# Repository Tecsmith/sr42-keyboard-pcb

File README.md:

# SR42 Keyboard

<p align="center">
Please refer to the <a href="https://github.com/Tecsmith/sr42-keyboard">project home</a> page for README and documentation.
</p>

---

<p align="center">
  <br>
  <b>Please Note:</b> This project is design complete, but has not been prototyped to validate. Build at your own risk.
</p>

---

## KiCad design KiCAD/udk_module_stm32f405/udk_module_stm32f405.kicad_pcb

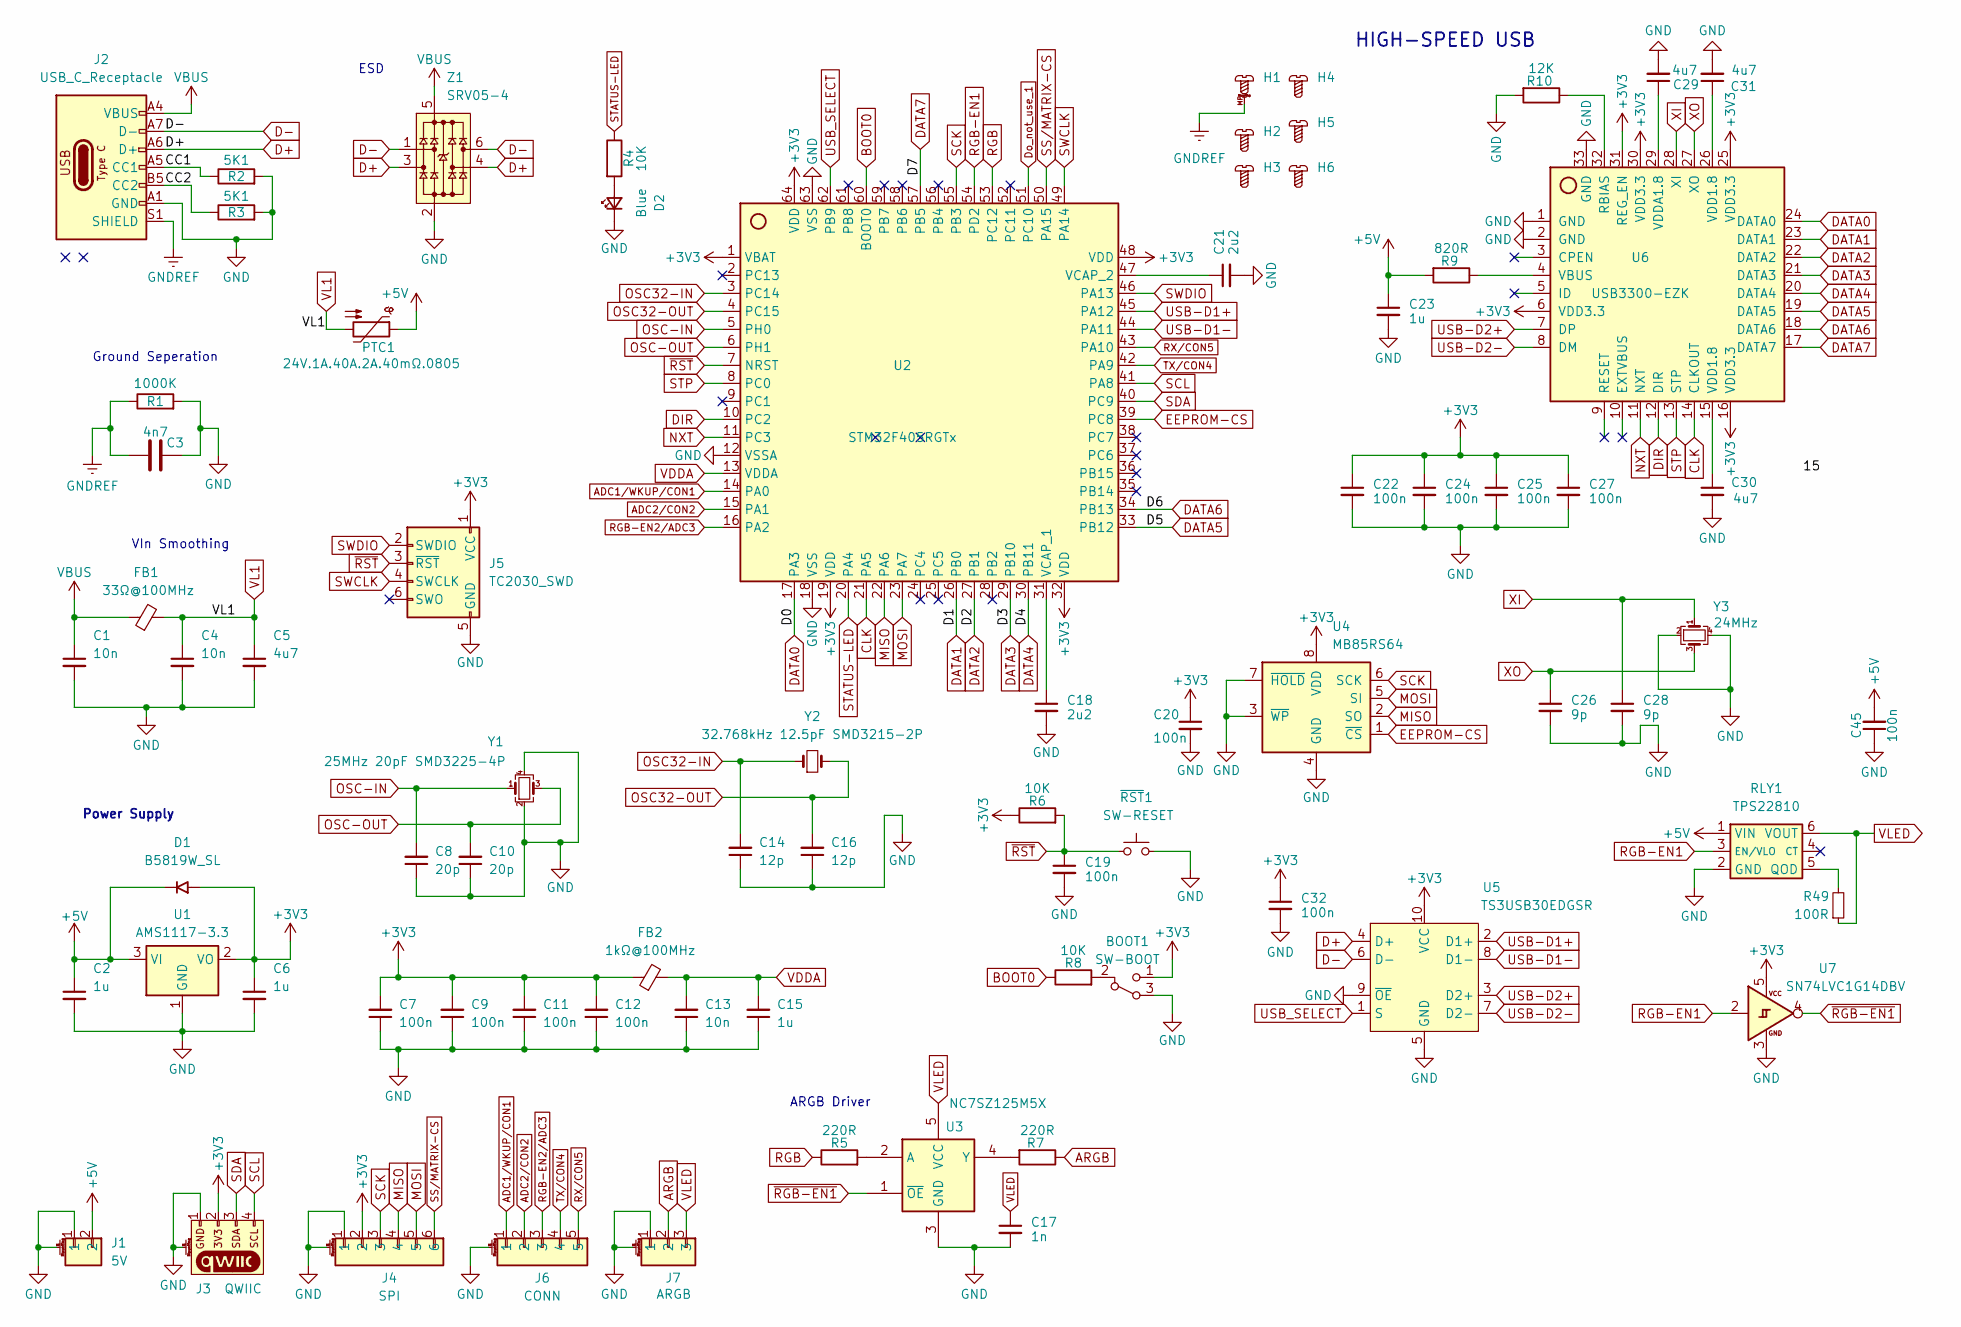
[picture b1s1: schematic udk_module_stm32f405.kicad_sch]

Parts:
BOOT1: SW-BOOT; SW_SPDT_Shouhan_MSK12C02; LCSC C431540
C1, C4, C13: 10n; C_0603_1608Metric
C2, C6, C15, C23: 1u; C_0603_1608Metric
C3: 4n7; C_0805_2012Metric_Pad1.18x1.45mm_HandSolder
C5, C29, C30, C31: 4u7; C_0603_1608Metric
C7, C9, C11, C12, C19, C20, C24, C25, C27, C32, C45: 100n; C_0603_1608Metric
C8, C10: 20p; C_0603_1608Metric
C14, C16: 12p; C_0603_1608Metric
C17: 1n; C_0603_1608Metric
C18, C21: 2u2; C_0603_1608Metric
C22: 100n; C_0603_1608Metric; Tolerance 100%
C26, C28: 9p; C_0603_1608Metric
D1: B5819W_SL; D_SOD-123
D2: Blue; LED_0603_1608Metric_Blue
FB1: 33Ω@100MHz; L_0603_1608Metric; LCSC C88984
FB2: 1kΩ@100MHz; L_0603_1608Metric
H1: Mount_M2_Rel
H2, H3, H4, H5, H6: Hole_M2
J1: 5V; JST_SH_SM02B-SRSS-TB_1x02-1MP_P1.00mm_Horizontal
J2: USB_C_Receptacle; USB_C_Receptacle_HRO_TYPE-C-31-M-12
J3: QWIIC; JST_SH_SM04B-SRSS-TB_1x04-1MP_P1.00mm_Horizontal
J4: SPI; JST_SH_SM06B-SRSS-TB_1x06-1MP_P1.00mm_Horizontal
J5: TC2030_SWD; CON_TC2030_outlined
J6: CONN; JST_SH_SM05B-SRSS-TB_1x05-1MP_P1.00mm_Horizontal
J7: ARGB; JST_SH_SM03B-SRSS-TB_1x03-1MP_P1.00mm_Horizontal
PTC1: 24V.1A.40A.2A.40mΩ.0805; L_Coilcraft_0805HQ_2012Metric; LCSC C42369218
R1: 1000K; R_0805_2012Metric_Pad1.20x1.40mm_HandSolder
R2, R3: 5K1; R_0603_1608Metric
R4, R6, R8: 10K; R_0603_1608Metric
R5, R7: 220R; R_0603_1608Metric
R9: 820R; R_0603_1608Metric
R10: 12K; R_0603_1608Metric
R49: 100R; R_0603_1608Metric
RLY1: TPS22810; SOT-23-6; LCSC C205990
U1: AMS1117-3.3; SOT-223-3_TabPin2
U2: STM32F405RGTx; LQFP-64_10x10mm_P0.5mm
U3: NC7SZ125M5X; SOT-23-5
U4: MB85RS64; SOIC-8_5.3x5.3mm_P1.27mm
U5: TS3USB30EDGSR; VSSOP-10_3x3mm_P0.5mm
U6: USB3300-EZK; QFN-32-1EP_5x5mm_P0.5mm_EP3.45x3.45mm
U7: SN74LVC1G14DBV; SOT-23-5
Y1: 25MHz 20pF SMD3225-4P; Crystal_SMD_3225-4Pin_3.2x2.5mm; LCSC C91738
Y2: 32.768kHz 12.5pF SMD3215-2P; Crystal_SMD_3215-2Pin_3.2x1.5mm; LCSC C156245
Y3: 24MHz; Crystal_SMD_3225-4Pin_3.2x2.5mm
Z1: SRV05-4; TSOP-6_1.65x3.05mm_P0.95mm
~{RST}1: SW-RESET; SW_SPST_CK_KMS2xxGP

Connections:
+3V3: BOOT1.1 (A), C6.1, C7.2, C9.2, C11.2, C12.2, C20.1, C22.1, C24.1, C25.1, C27.1, C32.1, D1.2 (A), FB2.1, J3.2, J4.2, J5.1 (VCC), R6.1, U1.2 (VO), U2.1 (VBAT), U2.19 (VDD), U2.32 (VDD), U2.48 (VDD), U2.64 (VDD), U4.8 (VDD), U5.10 (VCC), U6.6 (VDD3.3), U6.16 (VDD3.3), U6.25 (VDD3.3), U6.30 (VDD3.3), U6.31 (REG_EN), U7.5
+5V: C2.1, C23.1, C45.2, D1.1 (K), J1.2, PTC1.1, R9.2, RLY1.1 (VIN), U1.3 (VI)
/CC1: J2.A5 (CC1), R2.1
/CC2: J2.B5 (CC2), R3.1
ADC1/WKUP/CON1: J6.1, U2.14 (PA0)
ADC2/CON2: J6.2, U2.15 (PA1)
ARGB: J7.2, R7.1
BOOT0: R8.1, U2.60 (BOOT0)
CLK: U2.21 (PA5), U6.14 (CLKOUT)
D+: J2.A6 (D+), J2.B6 (D+), U5.4 (D+), Z1.3, Z1.4
D-: J2.A7 (D-), J2.B7 (D-), U5.6 (D-), Z1.1, Z1.6
DATA0: U2.17 (PA3), U6.24 (DATA0)
DATA1: U2.26 (PB0), U6.23 (DATA1)
DATA2: U2.27 (PB1), U6.22 (DATA2)
DATA3: U2.29 (PB10), U6.21 (DATA3)
DATA4: U2.30 (PB11), U6.20 (DATA4)
DATA5: U2.33 (PB12), U6.19 (DATA5)
DATA6: U2.34 (PB13), U6.18 (DATA6)
DATA7: U2.57 (PB5), U6.17 (DATA7)
DIR: U2.10 (PC2), U6.12 (DIR)
Do_not_use_1: U2.51 (PC10)
EEPROM-CS: U2.39 (PC8), U4.1 (~CS)
GND: BOOT1.3 (C), C1.2, C2.2, C3.2, C4.2, C5.2, C6.2, C7.1, C8.1, C9.1, C10.1, C11.1, C12.1, C13.1, C14.1, C15.1, C16.1, C17.2, C18.2, C19.2, C20.2, C21.2, C22.2, C23.2, C24.2, C25.2, C26.2, C27.2, C28.2, C29.2, C30.2, C31.2, C32.2, C45.1, D2.1 (K), J1.1, J1.MP, J2.A1 (GND), J2.A12 (GND), J2.B1 (GND), J2.B12 (GND), J3.1, J3.MP, J4.1, J4.MP, J5.5 (GND), J6.MP, J7.1, J7.MP, R1.2, R2.2, R3.2, R10.2, RLY1.2 (GND), U1.1 (GND), U2.12 (VSSA), U2.18 (VSS), U2.63 (VSS), U3.3 (GND), U4.3 (~WP), U4.4 (GND), U4.7 (~HOLD), U5.5 (GND), U5.9 (~OE), U6.1 (GND), U6.2 (GND), U6.33 (GND), U7.3, Y1.2, Y1.4, Y3.2, Y3.4, Z1.2, ~{RST}1.2
GNDREF: C3.1, H1.MP, J2.S1 (SHIELD), R1.1
MISO: J4.4, U2.22 (PA6), U4.2 (SO)
MOSI: J4.5, U2.23 (PA7), U4.5 (SI)
NXT: U2.11 (PC3), U6.11 (NXT)
unnamed: BOOT1.2 (B), R8.2
unnamed: C30.1, U6.15 (VDD1.8)
unnamed: C31.1, U6.26 (VDD1.8)
unnamed: D2.2 (A), R4.2
unnamed: R49.2, RLY1.5 (QOD)
unnamed: C18.1, U2.31 (VCAP_1)
unnamed: C21.1, U2.47 (VCAP_2)
unnamed: R5.2, U3.2 (A)
unnamed: R7.2, U3.4 (Y)
unnamed: R10.1, U6.32 (RBIAS)
unnamed: R9.1, U6.4 (VBUS)
unnamed: C29.1, U6.29 (VDDA1.8)
OSC32-IN: C14.2, U2.3 (PC14), Y2.1
OSC32-OUT: C16.2, U2.4 (PC15), Y2.2
OSC-IN: C8.2, U2.5 (PH0), Y1.1
OSC-OUT: C10.2, U2.6 (PH1), Y1.3
RGB: R5.1, U2.53 (PC12)
RGB-EN1: RLY1.3 (EN/VLO), U2.54 (PD2), U7.2
RGB-EN2/ADC3: J6.3, U2.16 (PA2)
RX/CON5: J6.5, U2.43 (PA10)
SCK: J4.3, U2.55 (PB3), U4.6 (SCK)
SCL: J3.4, U2.41 (PA8)
SDA: J3.3, U2.40 (PC9)
SS/MATRIX-CS: J4.6, U2.50 (PA15)
STATUS-LED: R4.1, U2.20 (PA4)
STP: U2.8 (PC0), U6.13 (STP)
SWCLK: J5.4 (SWCLK), U2.49 (PA14)
SWDIO: J5.2 (SWDIO), U2.46 (PA13)
TX/CON4: J6.4, U2.42 (PA9)
USB-D1+: U2.45 (PA12), U5.2 (D1+)
USB-D1-: U2.44 (PA11), U5.8 (D1-)
USB-D2+: U5.3 (D2+), U6.7 (DP)
USB-D2-: U5.7 (D2-), U6.8 (DM)
USB_SELECT: U2.62 (PB9), U5.1 (S)
VBUS: C1.1, FB1.1, J2.A4 (VBUS), J2.A9 (VBUS), J2.B4 (VBUS), J2.B9 (VBUS), Z1.5
VDDA: C13.2, C15.2, FB2.2, U2.13 (VDDA)
VL1: C4.1, C5.1, FB1.2, PTC1.2
VLED: C17.1, J7.3, R49.1, RLY1.6 (VOUT), U3.5 (VCC)
XI: C28.1, U6.28 (XI), Y3.1
XO: C26.1, U6.27 (XO), Y3.3
~RGB-EN1: U3.1 (~OE), U7.4
~RST: C19.1, J5.3 (~RST), R6.2, U2.7 (NRST), ~{RST}1.1

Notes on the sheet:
ESD
Ground Seperation
VIn Smoothing
Power Supply
ARGB Driver
HIGH-SPEED USB

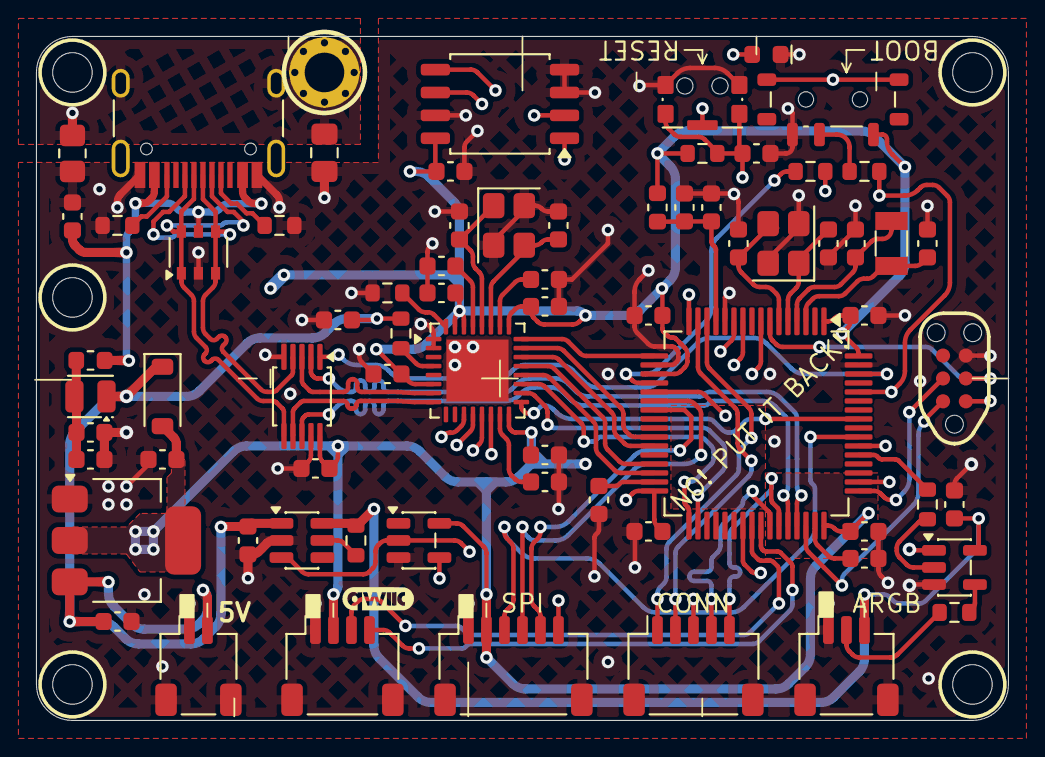
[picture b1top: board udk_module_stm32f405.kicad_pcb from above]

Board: 4 copper layers, 54.0 x 38.0 mm, 75 parts (0 on the bottom side), 68 nets.

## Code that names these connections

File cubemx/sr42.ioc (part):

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Mcu.Name=STM32F405RGTx
Mcu.Package=LQFP64
Mcu.UserName=STM32F405RGTx
PA0-WKUP.GPIOParameters=GPIO_Label
PA0-WKUP.GPIO_Label=ADC1/WKUP
PA0-WKUP.Signal=ADCx_IN0
PA1.GPIOParameters=GPIO_Label
PA1.GPIO_Label=ADC2
PA1.Signal=ADCx_IN1
PA10.GPIOParameters=GPIO_Label
PA10.GPIO_Label=RX/CON5
PA10.Mode=Asynchronous
PA10.Signal=USART1_RX
PA11.GPIOParameters=GPIO_Label
PA11.GPIO_Label=USB-D1-
PA11.Mode=Device_Only
PA11.Signal=USB_OTG_FS_DM
PA12.GPIOParameters=GPIO_Label
PA12.GPIO_Label=USB-D1+
PA12.Mode=Device_Only
PA12.Signal=USB_OTG_FS_DP
PA13.GPIOParameters=GPIO_Label
PA13.GPIO_Label=SWDIO
PA13.Mode=Serial_Wire
PA13.Signal=SYS_JTMS-SWDIO
PA14.GPIOParameters=GPIO_Label
PA14.GPIO_Label=SWCLK
PA14.Mode=Serial_Wire
PA14.Signal=SYS_JTCK-SWCLK
PA15.GPIOParameters=GPIO_Label
PA15.GPIO_Label=SS/MATRIX-CS
PA15.Mode=NSS_Signal_Hard_Output
PA15.Signal=SPI1_NSS
PA2.GPIOParameters=GPIO_Label
PA2.GPIO_Label=RGB-EN2/ADC3
PA2.Signal=ADCx_IN2
PA3.GPIOParameters=GPIO_Label
PA3.GPIO_Label=DATA0
PA3.Mode=Device_HS
PA3.Signal=USB_OTG_HS_ULPI_D0
PA4.GPIOParameters=GPIO_Label
PA4.GPIO_Label=STATUS-LED
PA4.Signal=GPIO_Output
PA5.GPIOParameters=GPIO_Label
PA5.GPIO_Label=CLK
PA5.Mode=Device_HS
PA5.Signal=USB_OTG_HS_ULPI_CK
PA6.GPIOParameters=GPIO_Label
PA6.GPIO_Label=MISO
PA6.Mode=Full_Duplex_Master
PA6.Signal=SPI1_MISO
PA7.GPIOParameters=GPIO_Label
PA7.GPIO_Label=MOSI
PA7.Mode=Full_Duplex_Master
PA7.Signal=SPI1_MOSI
PA8.GPIOParameters=GPIO_Label
PA8.GPIO_Label=SCL
PA8.Mode=I2C
PA8.Signal=I2C3_SCL
PA9.GPIOParameters=GPIO_Label
PA9.GPIO_Label=TX/CON4
PA9.Mode=Asynchronous
PA9.Signal=USART1_TX
PB0.GPIOParameters=GPIO_Label
PB0.GPIO_Label=DATA1
PB0.Mode=Device_HS
PB0.Signal=USB_OTG_HS_ULPI_D1
PB1.GPIOParameters=GPIO_Label
PB1.GPIO_Label=DATA2
PB1.Mode=Device_HS
PB1.Signal=USB_OTG_HS_ULPI_D2
PB10.GPIOParameters=GPIO_Label
PB10.GPIO_Label=DATA3
PB10.Mode=Device_HS
PB10.Signal=USB_OTG_HS_ULPI_D3
PB11.GPIOParameters=GPIO_Label
PB11.GPIO_Label=DATA4
PB11.Mode=Device_HS
PB11.Signal=USB_OTG_HS_ULPI_D4
PB12.GPIOParameters=GPIO_Label
PB12.GPIO_Label=DATA5
PB12.Mode=Device_HS
PB12.Signal=USB_OTG_HS_ULPI_D5
PB13.GPIOParameters=GPIO_Label
PB13.GPIO_Label=DATA6
PB13.Mode=Device_HS
PB13.Signal=USB_OTG_HS_ULPI_D6
PB3.GPIOParameters=GPIO_Label
PB3.GPIO_Label=SCK
PB3.Mode=Full_Duplex_Master
PB3.Signal=SPI1_SCK
PB5.GPIOParameters=GPIO_Label
PB5.GPIO_Label=DATA7
PB5.Mode=Device_HS
PB5.Signal=USB_OTG_HS_ULPI_D7
PB9.GPIOParameters=GPIO_Label
PB9.GPIO_Label=USB-SELECT
PB9.Signal=GPIO_Output
PC0.GPIOParameters=GPIO_Label
PC0.GPIO_Label=STP
PC0.Mode=Device_HS
PC0.Signal=USB_OTG_HS_ULPI_STP
PC10.GPIOParameters=GPIO_Label
PC10.GPIO_Label=Do_not_use_1
PC10.Mode=TX_Only_Simplex_Unidirect_Master
PC10.Signal=SPI3_SCK
PC12.GPIOParameters=GPIO_Label
PC12.GPIO_Label=RGB
PC12.Mode=TX_Only_Simplex_Unidirect_Master
PC12.Signal=SPI3_MOSI
PC14-OSC32_IN.GPIOParameters=GPIO_Label
PC14-OSC32_IN.GPIO_Label=OSC32-IN
PC14-OSC32_IN.Mode=LSE-External-Oscillator
PC14-OSC32_IN.Signal=RCC_OSC32_IN
PC15-OSC32_OUT.GPIOParameters=GPIO_Label
PC15-OSC32_OUT.GPIO_Label=OSC32-OUT
PC15-OSC32_OUT.Mode=LSE-External-Oscillator
PC15-OSC32_OUT.Signal=RCC_OSC32_OUT
PC2.GPIOParameters=GPIO_Label
PC2.GPIO_Label=DIR
PC2.Mode=Device_HS
PC2.Signal=USB_OTG_HS_ULPI_DIR
PC3.GPIOParameters=GPIO_Label
PC3.GPIO_Label=NXT
PC3.Mode=Device_HS
PC3.Signal=USB_OTG_HS_ULPI_NXT
PC8.GPIOParameters=GPIO_Label
PC8.GPIO_Label=EEPROM-CS
PC8.Signal=GPIO_Output
PC9.GPIOParameters=GPIO_Label
PC9.GPIO_Label=SDA
PC9.Mode=I2C
PC9.Signal=I2C3_SDA
PD2.GPIOParameters=GPIO_Label
PD2.GPIO_Label=RGB-EN1
PD2.Signal=GPIO_Output
PH0-OSC_IN.GPIOParameters=GPIO_Label
PH0-OSC_IN.GPIO_Label=OSC-IN
PH0-OSC_IN.Mode=HSE-External-Oscillator
PH0-OSC_IN.Signal=RCC_OSC_IN
PH1-OSC_OUT.GPIOParameters=GPIO_Label
PH1-OSC_OUT.GPIO_Label=OSC-OUT
PH1-OSC_OUT.Mode=HSE-External-Oscillator
PH1-OSC_OUT.Signal=RCC_OSC_OUT
RCC.HSE_VALUE=25000000
RCC.SYSCLKFreq_VALUE=168000000
RCC.SYSCLKSource=RCC_SYSCLKSOURCE_PLLCLK
board=custom

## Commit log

2025-11-23 Retire EAGLE
2025-11-23 wip-2025-11-23
2025-11-24 wip-2025-11-24
2025-11-25 wip-2025-11-25
2025-11-27 wip-2025-11-27
2025-11-28 wip-2025-11-28
2025-12-02 wip-2025-12-01
2026-01-14 UDK Version
2026-02-06 move rgb to spi pin
2026-06-13 june 2026 update
2026-06-13 move udk to seperate repo
2026-06-22 remove udk module
2026-06-22 folder move
2026-06-30 file moves

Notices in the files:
KiCAD/udk_module_stm32f405/udk_module_stm32f405.kicad_pcb:
© 2025 @SilvinoR
